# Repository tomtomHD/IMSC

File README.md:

# IMSC
*Sensor Interface for Soft Detectors in Surgical Simulators*

Thomas Thurner, 2023, <br/>
[thomas.thurner22@gmail.com](mailto:thomas.thurner22@gmail.com) <br/>
 <br/>
[Publication link](https://ieeexplore.ieee.org/abstract/document/10124724)
<br/>
<br/>
**Disclaimer**: <br/>
> The content of the data and files is provided “as is” without any warranty whatsoever, including the accuracy or comprehensiveness. Copyright holder of this document may change the contents of this document at any time without prior notice, and copyright holder disclaims any liability in relation to recipient’s use of this document.
The open source software in this product is distributed in the hope that it will be useful, but WITHOUT ANY WARRANTY; without even the implied warranty of MERCHANTABILITY or FITNESS FOR A PARTICULAR PURPOSE. <br/>

## Software license: MIT
software (C++/QT) license: GNU General Public License <br/>
hardware license: CERN OHL v2 Permissive <br/>
 <br/>
 <br/>
 
## Content:
1. CAD:
   - _SIC_Housing.step_ --> Housing of the Sensory Interface Circuit

3. Circuits: 
   - All Files: KiCad 6.0 Project files (https://www.kicad.org/)

4. Firmware: 
   - EIT_Arduino_V3 --> Folder including all firmware files (two Projects: ArduinoCore, EIT_Arduino_V3), via Microchip Studio 7.0.2542 (https://www.microchip.com/en-us/tools-resources/develop/microchip-studio) 
    - _EIT_Arduino_V3.atsln_ --> Atmel Studio Solution File 
   - _upload_to_proMicro_to_be_edited.bat_	--> File to upload resulting hex-file to microcontroller (to be edited: "Absolute_Path_To...\" needs to be replaced with the Path to the corresponding files) 

5. Software: 
   - Matlab_interface: 
     - _executeIMSC_basic.m_ --> Example code for running the SIC 
     - _IMSC.m_ --> Main file of SIC-class (working name is IMSC (Impedance Multi Sensing Circuit)) 
     - _imscData.m_ --> Data structure class of SIC 
     - _IDSerialComs.m_ --> Get list of COM-devices
   - Python_Interface: 
     - _executeIMSC_basic.py_ --> Example code for running the SIC
     - _executeIMSC_eit.py_ --> Example code for preparing the SIC for EIT
     - _ImpedanceMultiSensingCircuit.py_ --> Main file of SIC-class (working name is IMSC (Impedance Multi Sensing Circuit)) 
   - C++QT_Interface:
     - _impedancemultisensingcircuit.cpp_ --> cpp file
     - _impedancemultisensingcircuit.h_ --> header file

6. _Leakage_Correction_EIT.pdf_ --> Comparisons of the application of compensation strategy (equation 1) to uncompensated calculations by means of an EIT at different frequencies <br/>
 <br/>

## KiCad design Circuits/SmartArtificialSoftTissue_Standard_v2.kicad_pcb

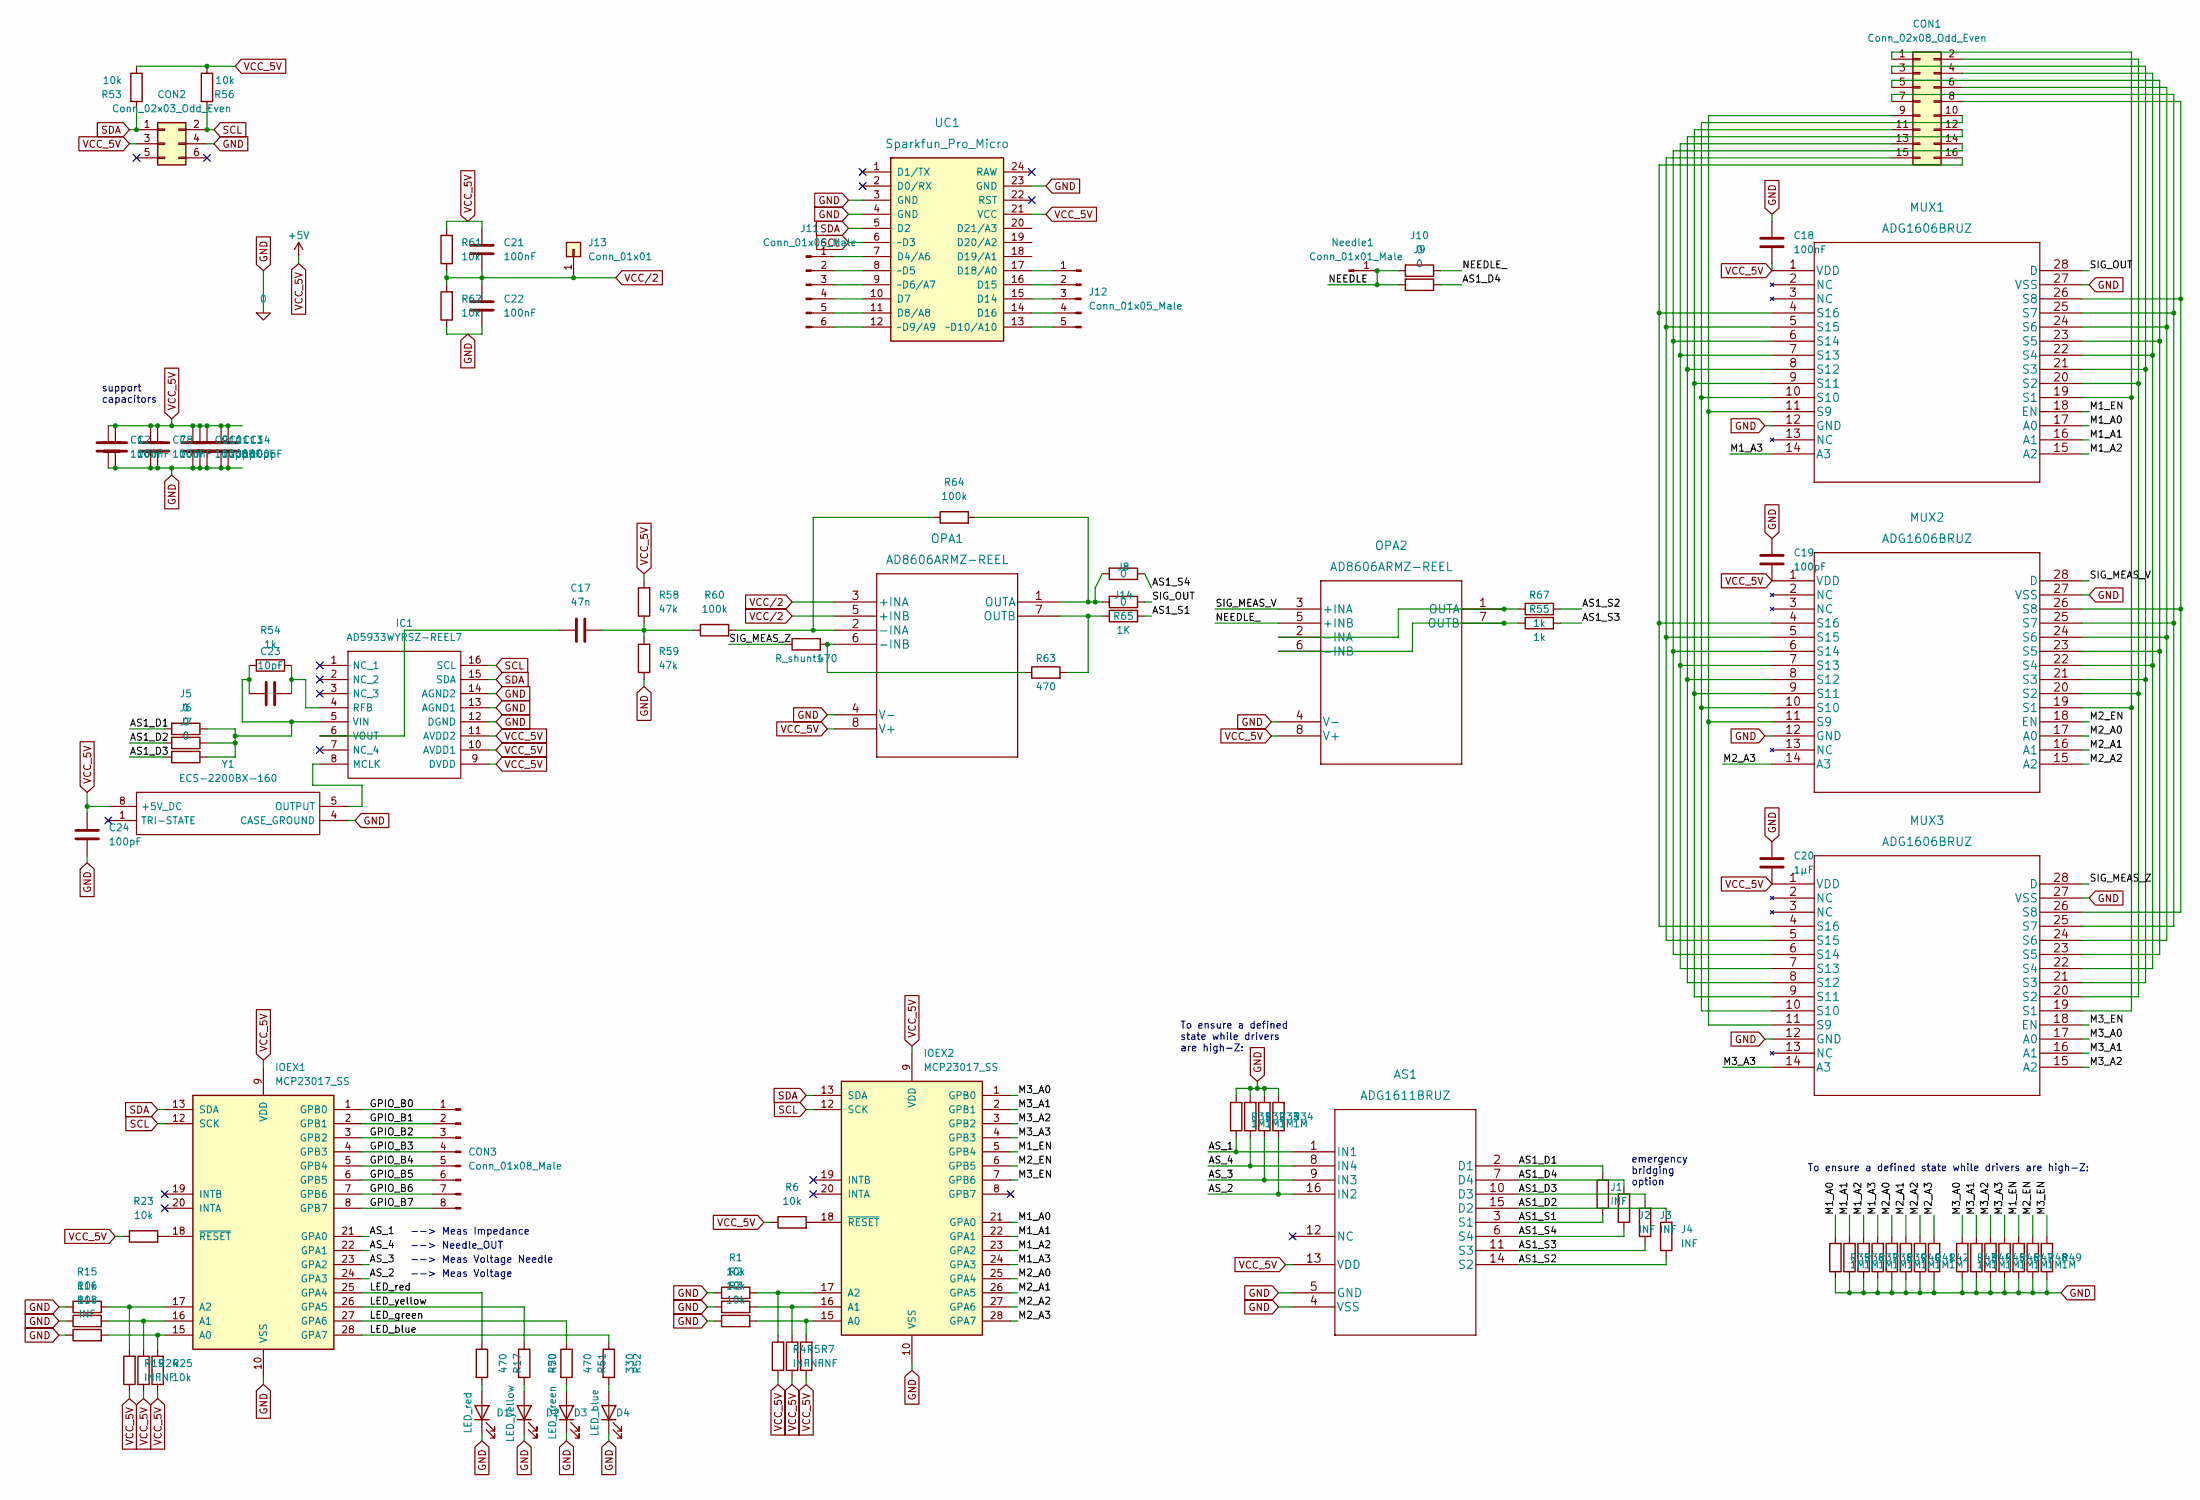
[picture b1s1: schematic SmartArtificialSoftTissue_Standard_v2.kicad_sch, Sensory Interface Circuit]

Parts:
AS1: ADG1611BRUZ; RU_16_ADI
C1, C2, C7, C8, C18, C21, C22: 100nF; C_0805_2012Metric_Pad1.18x1.45mm_HandSolder
C9, C10, C11, C13, C14: 100pF; C_0402_1005Metric_Pad0.74x0.62mm_HandSolder
C17: 47n; C_0805_2012Metric_Pad1.18x1.45mm_HandSolder
C19, C24: 100pF; C_0805_2012Metric_Pad1.18x1.45mm_HandSolder
C20: 1µF; C_0805_2012Metric_Pad1.18x1.45mm_HandSolder
C23: 10pF; C_0402_1005Metric_Pad0.74x0.62mm_HandSolder
CON1: Conn_02x08_Odd_Even; IDC-Header_2x08_P2.54mm_Vertical
CON2: Conn_02x03_Odd_Even; IDC-Header_2x03_P2.54mm_Vertical
CON3: Conn_01x08_Male; PinHeader_1x08_P2.54mm_Vertical
D1: LED_red; LED_0805_2012Metric_Pad1.15x1.40mm_HandSolder
D2: LED_yellow; LED_0805_2012Metric_Pad1.15x1.40mm_HandSolder
D3: LED_green; LED_0805_2012Metric_Pad1.15x1.40mm_HandSolder
D4: LED_blue; LED_0805_2012Metric_Pad1.15x1.40mm_HandSolder
IC1: AD5933WYRSZ-REEL7; SOP65P780X200-16N; Mouser Part Number 584-5933WYRSZR
IOEX1, IOEX2: MCP23017_SS; SSOP-28_5.3x10.2mm_P0.65mm
J1, J2, J3, J4: INF; R_0402_1005Metric_Pad0.72x0.64mm_HandSolder
J5, J6, J7, J8, J9, J10, J14: 0; R_0402_1005Metric_Pad0.72x0.64mm_HandSolder
J11: Conn_01x06_Male; PinHeader_1x06_P2.54mm_Vertical
J12: Conn_01x05_Male; PinHeader_1x05_P2.54mm_Vertical
J13: Conn_01x01; SolderWirePad_1x01_SMD_1x2mm
MUX1, MUX2, MUX3: ADG1606BRUZ; RU_28_ADI
Needle1: Conn_01x01_Male; Pin_D1.0mm_L10.0mm
OPA1, OPA2: AD8606ARMZ-REEL; RM_8_ADI
R1, R2, R3, R6, R15, R16, R23, R25, R53, R56, R61, R62: 10k; R_0402_1005Metric_Pad0.72x0.64mm_HandSolder
R4, R5, R7, R18, R19, R24: INF; R_0402_1005Metric_Pad0.72x0.64mm_HandSolder
R17, R50, R51, R63: 470; R_0402_1005Metric_Pad0.72x0.64mm_HandSolder
R31, R32, R33, R34, R35, R36, R37, R38, R39, R40, R41, R42, R43, R44, R45, R46, R47, R48, R49: 1M; R_0402_1005Metric_Pad0.72x0.64mm_HandSolder
R52: 330; R_0402_1005Metric_Pad0.72x0.64mm_HandSolder
R54, R55, R67: 1k; R_0402_1005Metric_Pad0.72x0.64mm_HandSolder
R58, R59: 47k; R_0402_1005Metric_Pad0.72x0.64mm_HandSolder
R60, R64: 100k; R_0402_1005Metric_Pad0.72x0.64mm_HandSolder
R65: 1K; R_0402_1005Metric_Pad0.72x0.64mm_HandSolder
R_shunt1: 470; R_0402_1005Metric_Pad0.72x0.64mm_HandSolder
UC1: Sparkfun_Pro_Micro
Y1: ECS-2200BX-160; ECS2200BX160; Mouser Part Number 520-2200BX-160

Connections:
/AS1_D1: AS1.2 (D1), J1.2, J5.2
/AS1_D2: AS1.15 (D2), J4.2, J6.2
/AS1_D3: AS1.10 (D3), J3.2, J7.2
/AS1_D4: AS1.7 (D4), J2.2, J9.1
/AS1_S1: AS1.3 (S1), J1.1, R65.2
/AS1_S2: AS1.14 (S2), J4.1, R67.2
/AS1_S3: AS1.11 (S3), J3.1, R55.2
/AS1_S4: AS1.6 (S4), J2.1, J8.1
/AS_1: AS1.1 (IN1), IOEX1.21 (GPA0), R31.1
/AS_2: AS1.16 (IN2), IOEX1.24 (GPA3), R34.1
/AS_3: AS1.9 (IN3), IOEX1.23 (GPA2), R33.1
/AS_4: AS1.8 (IN4), IOEX1.22 (GPA1), R32.1
/GPIO_B0: CON3.1, IOEX1.1 (GPB0)
/GPIO_B1: CON3.2, IOEX1.2 (GPB1)
/GPIO_B2: CON3.3, IOEX1.3 (GPB2)
/GPIO_B3: CON3.4, IOEX1.4 (GPB3)
/GPIO_B4: CON3.5, IOEX1.5 (GPB4)
/GPIO_B5: CON3.6, IOEX1.6 (GPB5)
/GPIO_B6: CON3.7, IOEX1.7 (GPB6)
/GPIO_B7: CON3.8, IOEX1.8 (GPB7)
/LED_blue: IOEX1.28 (GPA7), R52.1
/LED_green: IOEX1.27 (GPA6), R51.1
/LED_red: IOEX1.25 (GPA4), R17.1
/LED_yellow: IOEX1.26 (GPA5), R50.1
/M1_A0: IOEX2.21 (GPA0), MUX1.17 (A0), R35.2
/M1_A1: IOEX2.22 (GPA1), MUX1.16 (A1), R36.2
/M1_A2: IOEX2.23 (GPA2), MUX1.15 (A2), R37.2
/M1_A3: IOEX2.24 (GPA3), MUX1.14 (A3), R38.2
/M1_EN: IOEX2.5 (GPB4), MUX1.18 (EN), R47.2
/M2_A0: IOEX2.25 (GPA4), MUX2.17 (A0), R39.2
/M2_A1: IOEX2.26 (GPA5), MUX2.16 (A1), R40.2
/M2_A2: IOEX2.27 (GPA6), MUX2.15 (A2), R41.2
/M2_A3: IOEX2.28 (GPA7), MUX2.14 (A3), R42.2
/M2_EN: IOEX2.6 (GPB5), MUX2.18 (EN), R48.2
/M3_A0: IOEX2.1 (GPB0), MUX3.17 (A0), R43.2
/M3_A1: IOEX2.2 (GPB1), MUX3.16 (A1), R44.2
/M3_A2: IOEX2.3 (GPB2), MUX3.15 (A2), R45.2
/M3_A3: IOEX2.4 (GPB3), MUX3.14 (A3), R46.2
/M3_EN: IOEX2.7 (GPB6), MUX3.18 (EN), R49.2
/NEEDLE: J9.2, J10.2, Needle1.1
/NEEDLE_: J10.1, OPA2.5 (+INB)
/SIG_MEAS_V: MUX2.28 (D), OPA2.3 (+INA)
/SIG_MEAS_Z: MUX3.28 (D), R_shunt1.1
/SIG_OUT: J14.1, MUX1.28 (D)
GND: AS1.4 (VSS), AS1.5 (GND), C1.2, C2.2, C7.2, C8.2, C9.2, C10.2, C11.2, C13.2, C14.2, C18.1, C19.1, C20.1, C22.2, C24.2, CON2.4, D1.1 (K), D2.1 (K), D3.1 (K), D4.1 (K), IC1.12 (DGND), IC1.13 (AGND1), IC1.14 (AGND2), IOEX1.10 (VSS), IOEX2.10 (VSS), MUX1.12 (GND), MUX1.27 (VSS), MUX2.12 (GND), MUX2.27 (VSS), MUX3.12 (GND), MUX3.27 (VSS), OPA1.4 (V-), OPA2.4 (V-), R1.1, R2.1, R3.1, R15.1, R16.1, R18.1, R31.2, R32.2, R33.2, R34.2, R35.1, R36.1, R37.1, R38.1, R39.1, R40.1, R41.1, R42.1, R43.1, R44.1, R45.1, R46.1, R47.1, R48.1, R49.1, R59.1, R62.1, UC1.3 (GND), UC1.4 (GND), UC1.23 (GND), Y1.4 (CASE_GROUND)
unnamed: C17.1, IC1.6 (VOUT)
unnamed: C17.2, R58.1, R59.2, R60.1
unnamed: C23.1, IC1.5 (VIN), J5.1, J6.1, J7.1, R54.2
unnamed: C23.2, IC1.4 (RFB), R54.1
unnamed: CON1.1, MUX1.19 (S1), MUX2.19 (S1), MUX3.19 (S1)
unnamed: CON1.2, MUX1.20 (S2), MUX2.20 (S2), MUX3.20 (S2)
unnamed: CON1.3, MUX1.21 (S3), MUX2.21 (S3), MUX3.21 (S3)
unnamed: CON1.4, MUX1.22 (S4), MUX2.22 (S4), MUX3.22 (S4)
unnamed: CON1.5, MUX1.23 (S5), MUX2.23 (S5), MUX3.23 (S5)
unnamed: CON1.6, MUX1.24 (S6), MUX2.24 (S6), MUX3.24 (S6)
unnamed: CON1.7, MUX1.25 (S7), MUX2.25 (S7), MUX3.25 (S7)
unnamed: CON1.8, MUX1.26 (S8), MUX2.26 (S8), MUX3.26 (S8)
unnamed: CON1.9, MUX1.11 (S9), MUX2.11 (S9), MUX3.11 (S9)
unnamed: CON1.10, MUX1.10 (S10), MUX2.10 (S10), MUX3.10 (S10)
unnamed: CON1.11, MUX1.9 (S11), MUX2.9 (S11), MUX3.9 (S11)
unnamed: CON1.12, MUX1.8 (S12), MUX2.8 (S12), MUX3.8 (S12)
unnamed: CON1.13, MUX1.7 (S13), MUX2.7 (S13), MUX3.7 (S13)
unnamed: CON1.14, MUX1.6 (S14), MUX2.6 (S14), MUX3.6 (S14)
unnamed: CON1.15, MUX1.5 (S15), MUX2.5 (S15), MUX3.5 (S15)
unnamed: CON1.16, MUX1.4 (S16), MUX2.4 (S16), MUX3.4 (S16)
unnamed: D1.2 (A), R17.2
unnamed: D2.2 (A), R50.2
unnamed: D3.2 (A), R51.2
unnamed: D4.2 (A), R52.2
unnamed: IC1.8 (MCLK), Y1.5 (OUTPUT)
unnamed: IOEX1.15 (A0), R18.2, R25.2
unnamed: IOEX1.16 (A1), R16.2, R24.2
unnamed: IOEX1.17 (A2), R15.2, R19.2
unnamed: IOEX1.18 (~RESET), R23.2
unnamed: IOEX2.15 (A0), R3.2, R7.2
unnamed: IOEX2.16 (A1), R2.2, R5.2
unnamed: IOEX2.17 (A2), R1.2, R4.2
unnamed: IOEX2.18 (~RESET), R6.2
unnamed: J8.2, J14.2, OPA1.1 (OUTA), R64.2
unnamed: J11.1, UC1.7 (D4/A6)
unnamed: J11.2, UC1.8 (~D5)
unnamed: J11.3, UC1.9 (~D6/A7)
unnamed: J11.4, UC1.10 (D7)
unnamed: J11.5, UC1.11 (D8/A8)
unnamed: J11.6, UC1.12 (~D9/A9)
unnamed: J12.1, UC1.17 (D18/A0)
unnamed: J12.2, UC1.16 (D15)
unnamed: J12.3, UC1.15 (D14)
unnamed: J12.4, UC1.14 (D16)
unnamed: J12.5, UC1.13 (~D10/A10)
unnamed: OPA1.2 (-INA), R60.2, R64.1
unnamed: OPA1.6 (-INB), R63.1, R_shunt1.2
unnamed: OPA1.7 (OUTB), R63.2, R65.1
unnamed: OPA2.1 (OUTA), OPA2.2 (-INA), R67.1
unnamed: OPA2.6 (-INB), OPA2.7 (OUTB), R55.1
SCL: CON2.2, IC1.16 (SCL), IOEX1.12 (SCK), IOEX2.12 (SCK), R56.2, UC1.6 (~D3)
SDA: CON2.1, IC1.15 (SDA), IOEX1.13 (SDA), IOEX2.13 (SDA), R53.2, UC1.5 (D2)
VCC_5V: AS1.13 (VDD), C1.1, C2.1, C7.1, C8.1, C9.1, C10.1, C11.1, C13.1, C14.1, C18.2, C19.2, C20.2, C21.1, C24.1, CON2.3, IC1.9 (DVDD), IC1.10 (AVDD1), IC1.11 (AVDD2), IOEX1.9 (VDD), IOEX2.9 (VDD), MUX1.1 (VDD), MUX2.1 (VDD), MUX3.1 (VDD), OPA1.8 (V+), OPA2.8 (V+), R4.1, R5.1, R6.1, R7.1, R19.1, R23.1, R24.1, R25.1, R53.1, R56.1, R58.2, R61.2, UC1.21 (VCC), Y1.8 (+5V_DC)
VCC/2: C21.2, C22.1, J13.1, OPA1.3 (+INA), OPA1.5 (+INB), R61.1, R62.2

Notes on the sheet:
To ensure a defined state while drivers are high-Z:
--> Needle_OUT
support capacitors
--> Meas Voltage
emergency bridging option
--> Meas Impedance
To ensure a defined state while drivers are high-Z:
--> Meas Voltage Needle

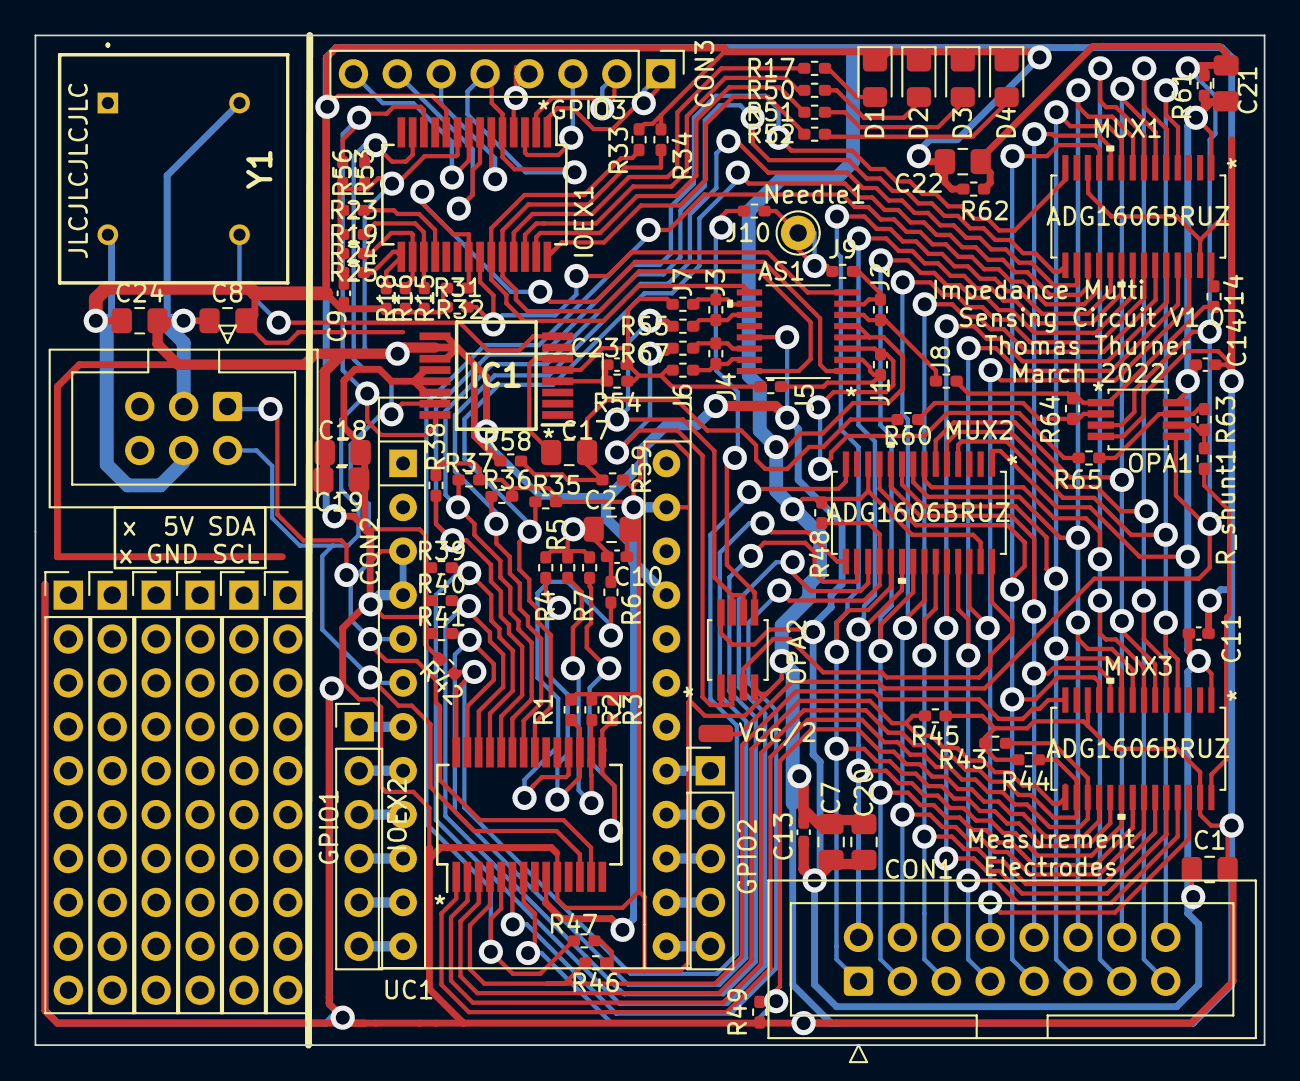
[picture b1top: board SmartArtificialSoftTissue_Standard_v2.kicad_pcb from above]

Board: 2 copper layers, 71.1 x 58.4 mm, 101 parts (0 on the bottom side), 99 nets.

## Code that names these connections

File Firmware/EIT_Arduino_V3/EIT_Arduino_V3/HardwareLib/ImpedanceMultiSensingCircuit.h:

/* 
* ImpedanceMultiSensingCircuit.h
*
* Created: 08.03.2022 23:06:42
* Author: Thomas Thurner
*/


#ifndef __IMPEDANCEMULTISENSINGCIRCUIT_H__
#define __IMPEDANCEMULTISENSINGCIRCUIT_H__

#include "MUX16_CIRCUIT.h"
#include "AD5933s.h"
#include "MCP23017.h"
#include "CircuitDataAndCorrectionValues.h"


//#define DEBUG_MODE




// AD5933 Options:
#define USE_INTERNAL_CLOCK		(false)
#define START_FREQ		(100000)
#define FREQ_INCR		(0)
#define NUM_INCR		(10)
#define MEASURE_NUMBER_PER_STIMULATION (13)
#define SETTLING_TIME_CYCLES (5)	// Waiting cycles until data is collected for the DFT
#define HP_SETTLING_TIME	(3)		// Wait ? ms until Signal is settled to steady state (HP)

// MCP23017 Addresses:
#define MCP23017_MUX_ADDR  (0)		// Address of MCP23017 controlling the Multiplexer
#define MCP23017_MODE_ADDR (1)		// Address of MCP23017 controlling the measurement-Mode, LEDs and GPIOs

// Voltages:
#define SIGNAL_VPP		(1.98)			// V

// Currents:
#define STIMULATION_CURRENT (1)			// mA

// Compensation tolerance:
#define COMPENSATIONTOLERANCE	(10)	// Tolerance; Outside this tolerance, compensation Values get updated and restored into EEPROM
#define COMPENSATION_DETERMINATION_SAFETY_REPETITIONS (3)		// Defines how often the same Result for compensation values has to be measured until they get accepted as valid

// Modes
#define MODE_Data_acquisition_finished	(0)
#define MODE_Magnitude_of_Voltage		(1)
#define MODE_Complex_Voltage			(2)
#define MODE_Magnitude_of_Impedance		(3)
#define MODE_Complex_Impedance			(4)
#define MODE_Magnitude_of_other_Data	(5)
#define MODE_Complex_other_Data			(6)
#define MODE_Magnitude_EIT_Data			(7)

// Gain-factors:
#define GAIN_R			(1.035e-07)						// Gain factor for calculating Impedance with standard circuit, calibrated with 'REF_RESIST = 3300 Ohm'

// Maximum HIGH-Z Values:
#define HIGH_Z_REAL_neg		(-50)
#define HIGH_Z_IMAG_pos		(300)

// ADG1611 Analog Switch:
#define ADG1611_LOG_ON		(0)
#define ADG1611_LOG_OFF		(HIGH)

// IO-Expander MODES PINOUT:
#define PIN_MODE_Z_MEAS_IN	(0)
#define PIN_MODE_V_MEAS_IN	(3)
#define PIN_MODE_NEEDLE_IN	(2)
#define PIN_MODE_NEEDLE_OUT	(1)
#define PIN_LED_RED			(4)
#define PIN_LED_YELLOW		(5)
#define PIN_LED_GREEN		(6)
#define PIN_LED_BLUE		(7)
// IO-Expander GPIO-Port-3 PINOUT:
#define GPIO_PORT_3_PIN_0   (0)
#define GPIO_PORT_3_PIN_1   (1)
#define GPIO_PORT_3_PIN_2   (2)
#define GPIO_PORT_3_PIN_3   (3)
#define GPIO_PORT_3_PIN_4   (4)
#define GPIO_PORT_3_PIN_5   (5)
#define GPIO_PORT_3_PIN_6   (6)
#define GPIO_PORT_3_PIN_7   (7)

// Needle Placeholder:
#define NEEDLE				(16)
//--------------------------------------------------------


//--------------------------------------------------------
// Class for LEDs:
class imsc_LED{
private:
	uint8_t pin;
	bool loglow;
	MCP23017* ioExpander;
	bool state;
public:
	imsc_LED(MCP23017* io_Expander, uint8_t pinIdx, bool logicalLow = LOW);
	~imsc_LED();
	void on();
	void off();
	bool getState();
	void overwrite(bool _state, byte* manipulateByteToSet = nullptr);
};

//--------------------------------------------------------

enum directPrintMode { DirectPRINT_NONE, DirectPRINT_MAGNITUDE, DirectPRINT_COMPLEX };
	
//--------------------------------------------------------
class ImpedanceMultiSensingCircuit
{
//variables

public:
	// Measurement-Pattern:
	uint8_t meas_pattern[MEASURE_NUMBER_PER_STIMULATION];
	
	// Stimulation-Pattern:
	uint8_t stim_pattern;	// Pattern
	uint8_t stim_current;	// Value
	
	// Result Vector of EIT (Voltage) measurement:
	float resultVsEIT[MEASURE_NUMBER_PER_STIMULATION] = {0};
		
	// Results (Temporary storage, can be both, Voltage or Impedance, depending of last measurement):
	float result_Real;
	float result_Imag;
	
	// Compensation Values:
	int16_t compensation_Z_Re;
	int16_t compensation_Z_Im;
	
	int16_t compensation_V_Re;
	int16_t compensation_V_Im;
	
	// Measurement Frequency:
	unsigned long measureFrequency;
		
private:
	// Max. measured DFT-value:
	float maxMeasuredDFT;
	
	// Gain factor for Ue(max)/DFT_value(max)  [ Ue..Output voltage of AD5933; DFT_value..calculated result of DFT in the AD5933]:
	float gain_U;
	// Gain factor for Impedance (1/Referenz_Impedance)/Reference_Magnitude:
	float gain_Z;
	
	// Indicator if signal generator is enabled:
	bool sigGenEnabled;
	
	// Last stimulation current measured:
	float lastMeasuredStimCurrent;
	
	// Temporary raw Data:
	float tempRawData[ELECTRODE_NUMBER+NEEDLE_NUMBER]; // (Electrodes + Needle)
	
	// Array to detect leakage currents (temporary):
	float leakageCurrentCompensationFactorA[ELECTRODE_NUMBER+NEEDLE_NUMBER] = {1};
	/*	At these measures, there is always only one pin/electrode with voltage (all others are highZ):
		All voltages get measured for a single pin stimulation and a Factor f is created to compensate the impact of leakage currents:
	    @Pin0 -> high:   {f0,f1,f2,f3,f4,...fN},
	*/
	
	
//objects
public:
		// Trinity MUX-object pointer:
		MUX16_CIRCUIT* trinityMUX; 
		
		// AD5933-object pointer:
		AD5933s* ad5933ciruit;
		
		// IO-Expander for Modes, LED and GPIO:
		MCP23017* mcp23017_ModeExpander;

private:
		// LED- and Modes:
		imsc_LED* redLED;
		imsc_LED* yellowLED;
		imsc_LED* greenLED;
		imsc_LED* blueLED;
		imsc_LED* analogSwitch_SIG_OUT_NEEDLE;
		imsc_LED* analogSwitch_V_MEAS_NEEDLE;
		imsc_LED* analogSwitch_V_MEAS;
		imsc_LED* analogSwitch_Z_MEAS;
		
		
//functions
public:
	// Constructor:
	ImpedanceMultiSensingCircuit();
	
	// Destructor:
	~ImpedanceMultiSensingCircuit();
	
	// Initialize Module for EIT:
	int8_t initIMSC();
	
	// Set electrode Initial conditions (separate as far as possible)
	void setElectrodeInitCond();
	
	// Self Calibration if nothing is connected (checked between Pin 0 and 1):
	void calibrationRoutine();
	
	// Write Modes and LED simultaneously:
	void writeModesAndLeds(byte byteToSet);
	
	// Send Data binary:
	void sendBinaryData(int8_t mode, int8_t fromEl = -1, int8_t toEl = -1, int8_t measEl = -1, float fData1 = NAN, float fData2 = NAN);
	
	// Set Module in Measurement-Mode:
	void beginMeasure();
	
	// Set Module in Standby-Mode (all Disabled):
	void endMeasure();
	
	// Main Measure Parts (Mind to "beginMeasure()" before and "endMeasure()" afterwards):
	float measureImpedance(int8_t fromEl, int8_t toEl, directPrintMode measureImpedance_directPrint_MODE = DirectPRINT_NONE);	// Return Magnitude of Impedance, Resistance and Reactance get stored in result_Real and result_Imag (including shunt Resistance and small Phase shift of System)
	float measureReactance(int8_t fromEl, int8_t toEl, directPrintMode measureReactance_directPrint_MODE = DirectPRINT_NONE);	// Return Reactance,			  Resistance and Reactance get stored in result_Real and result_Imag (including shunt Resistance and small Phase shift of System)
	float measureResistance(int8_t fromEl, int8_t toEl,directPrintMode measureResistance_directPrint_MODE= DirectPRINT_NONE);	// Return Resistance,			  Resistance and Reactance get stored in result_Real and result_Imag (including shunt Resistance and small Phase shift of System)
	
	float measureVoltage(int8_t measuringEl, int8_t stimSig, int8_t stimGnd, directPrintMode measureVoltage_directPrint_MODE, bool correctLeakage = false);
	
	// Disable all Modes (disable all analog switches):
	void disableModes();
	
	// Measure all electrodes, results are going to be written into result (Stimulation or similar must be prepared before):
	void measureAllPrepreparedV(directPrintMode measureAllVolt_directPrint_MODE = DirectPRINT_NONE);

	// Acquire data via Stimulation pattern and Measurement pattern (binary):
	void acquireEITdata(directPrintMode aquireData_directPrint_MODE = DirectPRINT_NONE, bool compensateLeakage = true, bool measureStimCurrent = true);
	
	// Prepare stimulation-electrodes (binary):
	void prepareStimulation();
	
	// Get last measured Stimulation current:
	float getLastMeasuredStimCurrent();
	
	// Get gain_U:
	float getGainU();
	
	// Get gain_Z
	float getGainZ();
	
protected:
private:


	// Measure Compensation Values !IF! nothing is connected:
	void determineCompensationValues();
	
	// Refresh max. measurable DFT-Value int 'maxMeasuredDFT'
	void getMaxMeasuredDFT();

	// Determine GAIN for Impedance Measurement:
	void determineGainZ();
	

	// Refresh leakageCurrentCompensationFactorA [Array] to compensate leakage currents / their impact  (binary):
	void getLeakageImpactVs();
	
	// Leakage correction (binary):
	void correctLeakingDataVs();
	
	ImpedanceMultiSensingCircuit( const ImpedanceMultiSensingCircuit &c );
	ImpedanceMultiSensingCircuit& operator=( const ImpedanceMultiSensingCircuit &c );
	

}; //ImpedanceMultiSensingCircuit



#endif //__IMPEDANCEMULTISENSINGCIRCUIT_H__

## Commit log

2023-03-31 Create software-LICENSE
2023-03-31 Create hardware-LICENSE
2023-09-12 Update README.md
    Publication link added.
2023-09-13 Update README.md
    email changed
2023-09-27 Update ImpedanceMultiSensingCircuit.py
    Input facilitated
2024-12-19 C++/QT
    C++ class implemented via QT-framework (blocking implementation, should be executed in a separate thread).
2024-12-19 Update README.md
    license for new files updated
2024-12-19 Update README.md
    Line-breaks added
2024-12-19 Update README.md
    formatting of text within README

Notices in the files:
parts and their libraries:
Copyright 2021 Accelerated Designs. All rights reserved.
